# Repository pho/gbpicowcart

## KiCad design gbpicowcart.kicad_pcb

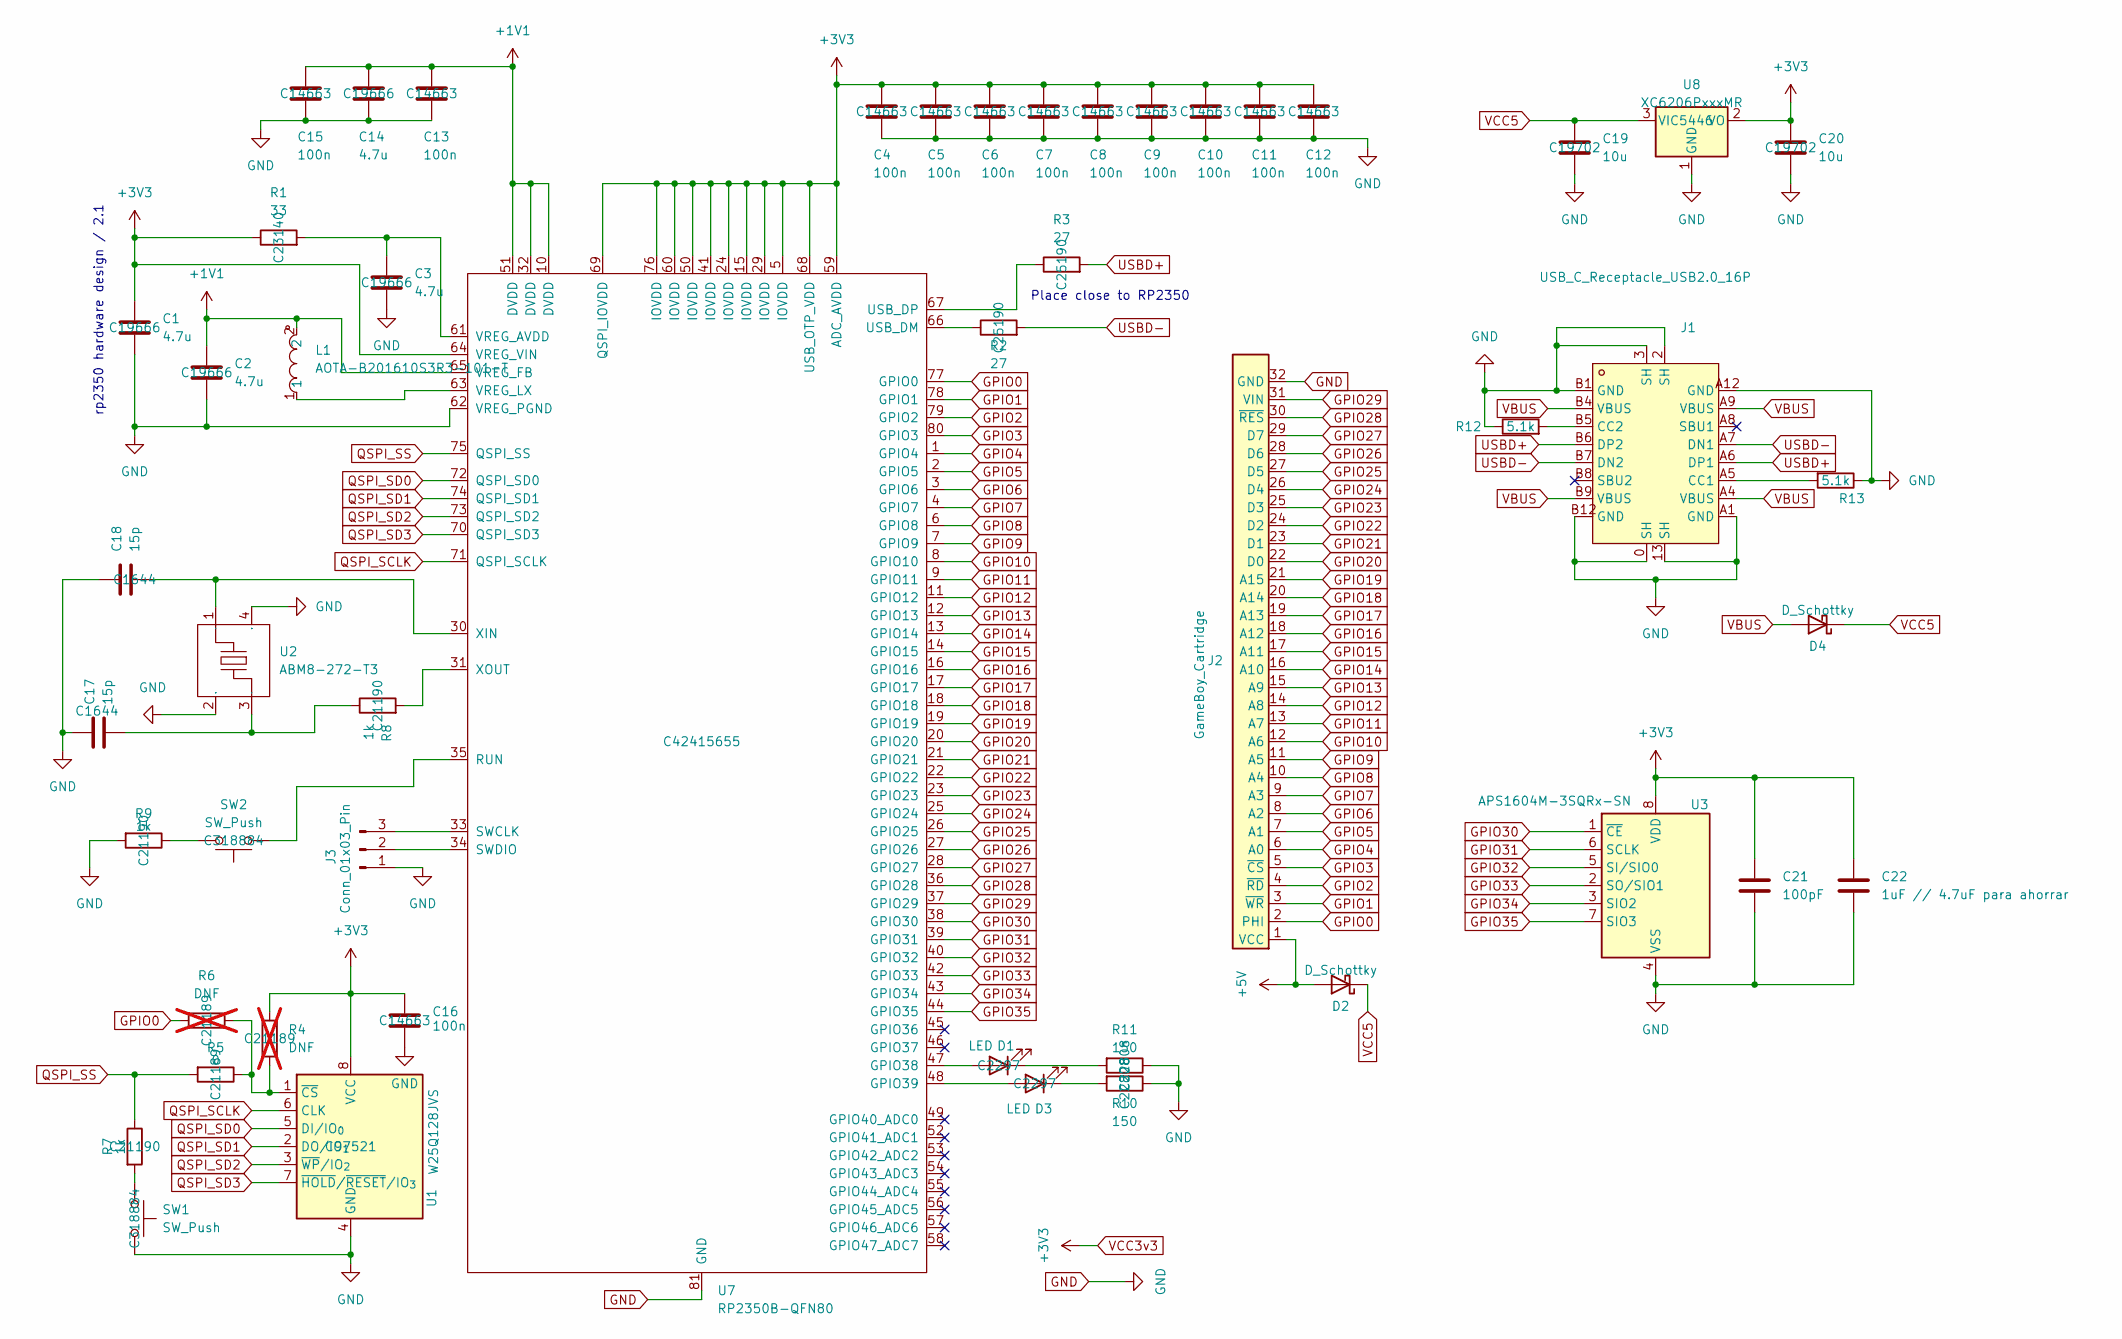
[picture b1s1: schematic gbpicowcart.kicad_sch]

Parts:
C1, C2, C3, C14: 4.7u; C_0603_1608Metric; LCSC C19666
C4, C5, C6, C7, C8, C9, C10, C11, C12, C13, C15, C16: 100n; C_0603_1608Metric; LCSC C14663
C17, C18: 15p; C_0603_1608Metric; LCSC C1644
C19, C20: 10u; C_0603_1608Metric; LCSC C19702
C21: 100pF; C_0603_1608Metric
C22: 1uF // 4.7uF para ahorrar; C_0603_1608Metric
D1, D3: LED; LED_0805_2012Metric; LCSC C2297
D2, D4: D_Schottky; D_SOD-123; LCSC C8598
J1: USB_C_Receptacle_USB2.0_16P; USB-C_SMD-TYPE-C-31-M-12; LCSC C2927038
J2: GameBoy_Cartridge; GameBoy_Cartridge_1x32_P1.50mm_Edge
J3: Conn_01x03_Pin; PinHeader_1x03_P2.54mm_Vertical
L1: AOTA-B201610S3R3-101-T; IND-SMD_L2.0-W1.6_AOTA-B201610S3R3-101-T; LCSC Part C42411119
R1: 33; R_0603_1608Metric; LCSC C23140
R2, R3: 27; R_0603_1608Metric; LCSC C25190
R4, R6: DNF; R_0603_1608Metric; LCSC C21189; not fitted
R5: 0; R_0603_1608Metric; LCSC C21189
R7, R8, R9: 1k; R_0603_1608Metric; LCSC C21190
R10, R11: 150; R_0603_1608Metric; LCSC C22808
R12, R13: 5.1k; R_0603_1608Metric; LCSC C23186
SW1, SW2: SW_Push; SW_SPST_SKQG_WithStem; LCSC C318884
U1: W25Q128JVS; SOIC-8_5.3x5.3mm_P1.27mm; LCSC C97521
U2: ABM8-272-T3; CRYSTAL-SMD_4P-L3.2-W2.5-BL; Manufacturer Part ABM8-272-T3; LCSC Part Name ABM8-272-T3
U3: APS1604M-3SQRx-SN; SOIC-8_3.9x4.9mm_P1.27mm
U7: RP2350B-QFN80; RP2350B_QFN-80_EP_10.573x10.573_Pitch0.4mm; LCSC C42415655
U8: XC6206PxxxMR; SOT-23-3; LCSC C5446

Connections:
+1V1: C2.1, C13.1, C14.1, C15.1, L1.2, U7.10 (DVDD), U7.32 (DVDD), U7.51 (DVDD), U7.65 (VREG_FB)
+5V: D2.2 (A), J2.1 (VCC)
GND: C1.2, C2.2, C3.2, C4.2, C5.2, C6.2, C7.2, C8.2, C9.2, C10.2, C11.2, C12.2, C13.2, C14.2, C15.2, C16.2, C17.1, C18.1, C19.2, C20.2, C21.2, C22.2, J1.0 (SH), J1.2 (SH), J1.3 (SH), J1.13 (SH), J1.A1 (GND), J1.A12 (GND), J1.B1 (GND), J1.B12 (GND), J2.32 (GND), J3.1, R9.2, R10.1, R11.1, R12.1, R13.1, SW1.2, U1.4 (GND), U2.2 (GND), U2.4 (GND), U3.4 (VSS), U7.62 (VREG_PGND), U7.81 (GND), U8.1 (GND)
GPIO0: J2.2 (PHI), R6.2, U7.77 (GPIO0)
GPIO1: J2.3 (~WR), U7.78 (GPIO1)
GPIO2: J2.4 (~RD), U7.79 (GPIO2)
GPIO3: J2.5 (~CS), U7.80 (GPIO3)
GPIO4: J2.6 (A0), U7.1 (GPIO4)
GPIO5: J2.7 (A1), U7.2 (GPIO5)
GPIO6: J2.8 (A2), U7.3 (GPIO6)
GPIO7: J2.9 (A3), U7.4 (GPIO7)
GPIO8: J2.10 (A4), U7.6 (GPIO8)
GPIO9: J2.11 (A5), U7.7 (GPIO9)
GPIO10: J2.12 (A6), U7.8 (GPIO10)
GPIO11: J2.13 (A7), U7.9 (GPIO11)
GPIO12: J2.14 (A8), U7.11 (GPIO12)
GPIO13: J2.15 (A9), U7.12 (GPIO13)
GPIO14: J2.16 (A10), U7.13 (GPIO14)
GPIO15: J2.17 (A11), U7.14 (GPIO15)
GPIO16: J2.18 (A12), U7.16 (GPIO16)
GPIO17: J2.19 (A13), U7.17 (GPIO17)
GPIO18: J2.20 (A14), U7.18 (GPIO18)
GPIO19: J2.21 (A15), U7.19 (GPIO19)
GPIO20: J2.22 (D0), U7.20 (GPIO20)
GPIO21: J2.23 (D1), U7.21 (GPIO21)
GPIO22: J2.24 (D2), U7.22 (GPIO22)
GPIO23: J2.25 (D3), U7.23 (GPIO23)
GPIO24: J2.26 (D4), U7.25 (GPIO24)
GPIO25: J2.27 (D5), U7.26 (GPIO25)
GPIO26: J2.28 (D6), U7.27 (GPIO26)
GPIO27: J2.29 (D7), U7.28 (GPIO27)
GPIO28: J2.30 (~RES), U7.36 (GPIO28)
GPIO29: J2.31 (VIN), U7.37 (GPIO29)
GPIO30: U3.1 (~CE), U7.38 (GPIO30)
GPIO31: U3.6 (SCLK), U7.39 (GPIO31)
GPIO32: U3.5 (SI/SIO0), U7.40 (GPIO32)
GPIO33: U3.2 (SO/SIO1), U7.42 (GPIO33)
GPIO34: U3.3 (SIO2), U7.43 (GPIO34)
GPIO35: U3.7 (SIO3), U7.44 (GPIO35)
unnamed: C17.2, R8.1, U2.3
unnamed: D1.2 (A), U7.47 (GPIO38)
unnamed: D1.1 (K), R11.2
unnamed: D3.2 (A), U7.48 (GPIO39)
unnamed: D3.1 (K), R10.2
unnamed: J1.A5 (CC1), R13.2
unnamed: J1.B5 (CC2), R12.2
unnamed: J3.2, U7.34 (SWDIO)
unnamed: J3.3, U7.33 (SWCLK)
unnamed: R7.2, SW1.1
unnamed: R9.1, SW2.2
unnamed: R4.2, R5.1, R6.1, U1.1 (~CS)
unnamed: SW2.1, U7.35 (RUN)
unnamed: R2.1, U7.66 (USB_DM)
unnamed: R3.1, U7.67 (USB_DP)
unnamed: C3.1, R1.2, U7.61 (VREG_AVDD)
unnamed: L1.1, U7.63 (VREG_LX)
unnamed: C18.2, U2.1, U7.30 (XIN)
unnamed: R8.2, U7.31 (XOUT)
QSPI_SCLK: U1.6 (CLK), U7.71 (QSPI_SCLK)
QSPI_SD0: U1.5 (DI/IO_{0}), U7.72 (QSPI_SD0)
QSPI_SD1: U1.2 (DO/IO_{1}), U7.74 (QSPI_SD1)
QSPI_SD2: U1.3 (~WP/IO_{2}), U7.73 (QSPI_SD2)
QSPI_SD3: U1.7 (~HOLD/~RESET/IO_{3}), U7.70 (QSPI_SD3)
QSPI_SS: R5.2, R7.1, U7.75 (QSPI_SS)
USBD+: J1.A6 (DP1), J1.B6 (DP2), R3.2
USBD-: J1.A7 (DN1), J1.B7 (DN2), R2.2
VBUS: D4.2 (A), J1.A4 (VBUS), J1.A9 (VBUS), J1.B4 (VBUS), J1.B9 (VBUS)
VCC3v3: C1.1, C4.1, C5.1, C6.1, C7.1, C8.1, C9.1, C10.1, C11.1, C12.1, C16.1, C20.1, C21.1, C22.1, R1.1, R4.1, U1.8 (VCC), U3.8 (VDD), U7.5 (IOVDD), U7.15 (IOVDD), U7.24 (IOVDD), U7.29 (IOVDD), U7.41 (IOVDD), U7.50 (IOVDD), U7.59 (ADC_AVDD), U7.60 (IOVDD), U7.64 (VREG_VIN), U7.68 (USB_OTP_VDD), U7.69 (QSPI_IOVDD), U7.76 (IOVDD), U8.2 (VO)
VCC5: C19.1, D2.1 (K), D4.1 (K), U8.3 (VI)

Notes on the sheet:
rp2350 hardware design / 2.1
Place close to RP2350

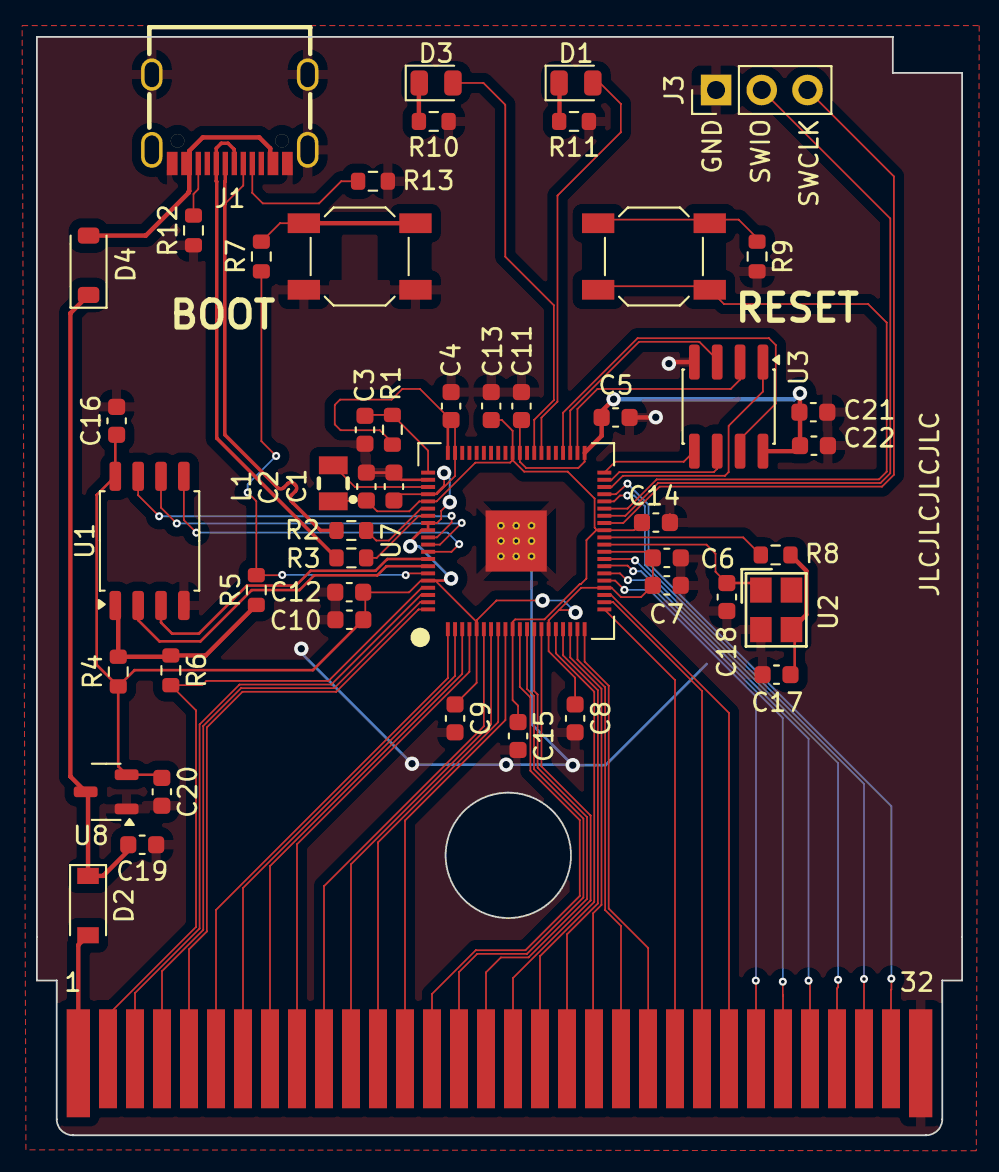
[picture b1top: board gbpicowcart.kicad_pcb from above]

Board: 2 copper layers, 51.4 x 61.0 mm, 50 parts (0 on the bottom side), 69 nets.

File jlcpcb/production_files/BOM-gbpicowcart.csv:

Comment,Designator,Footprint,LCSC,Quantity
100n,"C10,C11,C12,C13,C15,C16,C4,C5,C6,C7,C8,C9",C_0603_1608Metric,C14663,12
15p,"C17,C18",C_0603_1608Metric,C1644,2
4.7u,"C1,C14,C2,C3",C_0603_1608Metric,C19666,4
10u,"C19,C20",C_0603_1608Metric,C19702,2
ABM8-272-T3,U2,CRYSTAL-SMD_4P-L3.2-W2.5-BL,C20625731,1
DNF,R5,R_0603_1608Metric,C21189,1
1k,"R7,R8,R9",R_0603_1608Metric,C21190,3
150,"R10,R11",R_0603_1608Metric,C22808,2
LED,"D1,D3",LED_0805_2012Metric,C2297,2
33,R1,R_0603_1608Metric,C23140,1
5.1k,"R12,R13",R_0603_1608Metric,C23186,2
27,"R2,R3",R_0603_1608Metric,C25190,2
USB_C_Receptacle_USB2.0_16P,J1,USB-C_SMD-TYPE-C-31-M-12,C2927038,1
SW_Push,"SW1,SW2",SW_SPST_SKQG_WithStem,C318884,2
AOTA-B201610S3R3-101-T,L1,IND-SMD_L2.0-W1.6_AOTA-B201610S3R3-101-T,C42411119,1
RP2350B-QFN80,U7,RP2350B_QFN-80_EP_10.573x10.573_Pitch0.4mm,C42415655,1
XC6206PxxxMR,U8,SOT-23-3,C5446,1
D_Schottky,D2,D_SOD-123,C8598,1
W25Q128JVS,U1,SOIC-8_5.3x5.3mm_P1.27mm,C97521,1

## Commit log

2022-07-11 schematic seems done
2023-03-05 Remapped footprints for the first fabrication test
2023-03-05 Added 3D render
2025-09-18 rehecho y fabricado, pero algunos bugardillos veo
2025-09-24 Removing level shifters and switch to usbc
2025-09-24 simplify labels
2025-09-29 seems ready to do another run
2026-06-05 added PSRAM and a usb vbus diode
